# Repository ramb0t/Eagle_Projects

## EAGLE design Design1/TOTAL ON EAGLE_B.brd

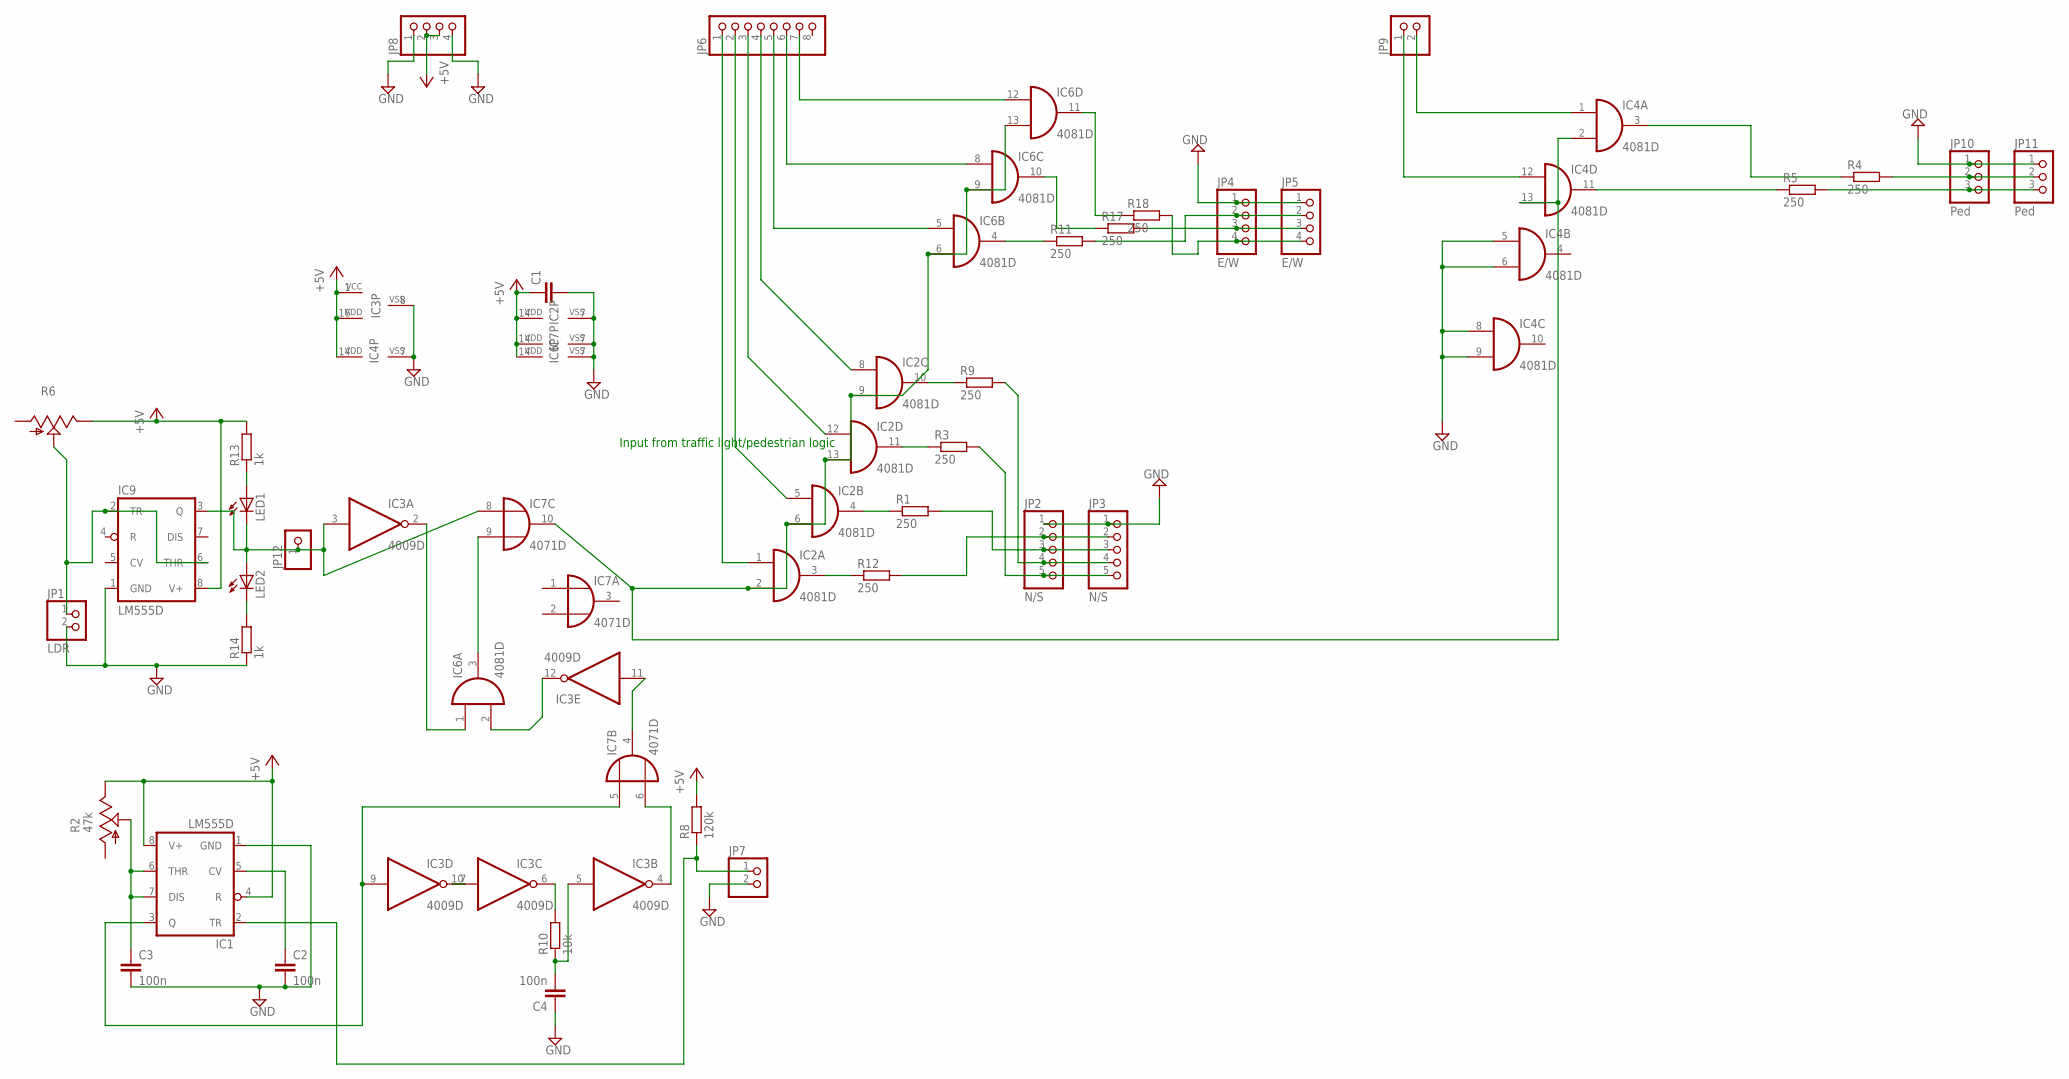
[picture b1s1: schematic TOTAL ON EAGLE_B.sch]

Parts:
C1: C-EUC0805; C0805
C2, C3, C4: 100n; C0805
IC1, IC9: LM555D; SO08
IC2, IC4, IC6: 4081D; SO14
IC3: 4009D; SO16
IC7: 4071D; SO14
JP1: LDR; 1X02
JP2, JP3: N/S; 1X05
JP4, JP5: E/W; 1X04
JP6: PINHD-1X8; 1X08
JP7, JP9: PINHD-1X2; 1X02
JP8: PINHD-1X4; 1X04
JP10, JP11: Ped; 1X03
JP12: PINHD-1X1; 1X01
LED1, LED2: LEDSML0805; SML0805
R1, R3, R4, R5, R9, R11, R12, R17, R18: 250; M0805
R2: 47k; B64W
R6: TRIM_US-B25P; B25P
R8: 120k; M0805
R10: 10k; M0805
R13, R14: 1k; M0805

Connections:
+5V: C1.1, IC1.4 (R), IC1.8 (V+), IC2.14 (VDD), IC3.1 (VCC), IC3.16 (VDD), IC4.14 (VDD), IC6.14 (VDD), IC7.14 (VDD), IC9.8 (V+), JP8.2, JP8.3, R2.E, R6.E, R8.2, R13.2
GND: C1.2, C2.2, C3.2, C4.1, IC1.1 (GND), IC2.7 (VSS), IC3.8 (VSS), IC4.5 (I0), IC4.6 (I1), IC4.7 (VSS), IC4.8 (I0), IC4.9 (I1), IC6.7 (VSS), IC7.7 (VSS), IC9.1 (GND), JP1.2, JP2.1, JP3.1, JP4.1, JP5.1, JP7.2, JP8.1, JP8.4, JP10.1, JP11.1, R14.1
unnamed: C2.1, IC1.5 (CV)
unnamed: IC2.4 (O), R1.1
unnamed: IC3.4 (O), IC7.6 (I1)
unnamed: IC2.3 (O), R12.1
unnamed: JP2.3, JP3.3, R1.2
unnamed: JP10.2, JP11.2, R4.2
unnamed: JP10.3, JP11.3, R5.2
unnamed: JP4.3, JP5.3, R17.2
unnamed: IC4.12 (I0), JP9.1
unnamed: IC4.1 (I0), JP9.2
unnamed: IC2.11 (O), R3.1
unnamed: IC4.3 (O), R4.1
unnamed: JP2.5, JP3.5, R3.2
unnamed: IC1.2 (TR), JP7.1, R8.1
unnamed: IC4.11 (O), R5.1
unnamed: IC2.10 (O), R9.1
unnamed: IC1.3 (Q), IC3.9 (I), IC7.5 (I0)
unnamed: JP2.4, JP3.4, R9.2
unnamed: IC3.2 (O), IC6.1 (I0)
unnamed: IC6.3 (O), IC7.9 (I1)
unnamed: IC3.12 (O), IC6.2 (I1)
unnamed: C3.1, IC1.6 (THR), IC1.7 (DIS), R2.S
unnamed: IC3.7 (I), IC3.10 (O)
unnamed: C4.2, IC3.5 (I), R10.1
unnamed: IC2.2 (I1), IC2.6 (I1), IC2.9 (I1), IC2.13 (I1), IC4.2 (I1), IC4.13 (I1), IC6.6 (I1), IC6.9 (I1), IC6.13 (I1), IC7.10 (O)
unnamed: IC2.1 (I0), JP6.1
unnamed: LED1.A, R13.1
unnamed: IC3.3 (I), IC7.8 (I0), IC9.3 (Q), JP12.1, LED1.C, LED2.A
unnamed: LED2.C, R14.2
unnamed: IC3.6 (O), R10.2
unnamed: IC9.2 (TR), IC9.6 (THR), JP1.1, R6.S
unnamed: IC2.5 (I0), JP6.2
unnamed: IC2.12 (I0), JP6.3
unnamed: IC2.8 (I0), JP6.4
unnamed: IC6.5 (I0), JP6.5
unnamed: JP2.2, JP3.2, R12.2
unnamed: IC6.8 (I0), JP6.6
unnamed: IC6.12 (I0), JP6.7
unnamed: JP4.4, JP5.4, R18.2
unnamed: IC3.11 (I), IC7.4 (O)
unnamed: IC6.11 (O), R18.1
unnamed: IC6.10 (O), R17.1
unnamed: JP4.2, JP5.2, R11.2
unnamed: IC6.4 (O), R11.1

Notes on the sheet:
Input from traffic light/pedestrian logic

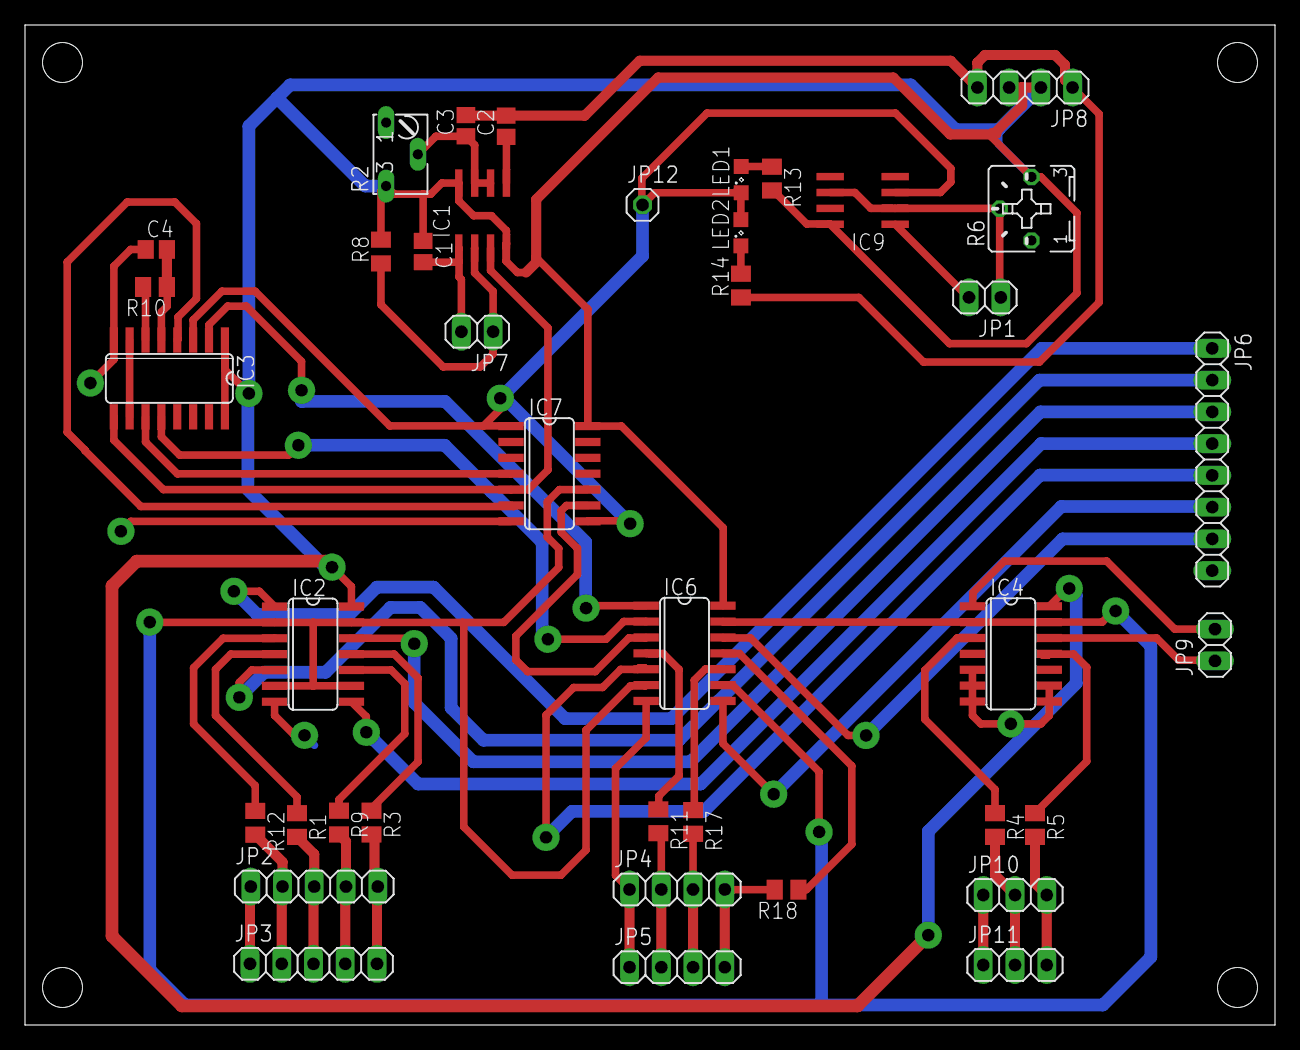
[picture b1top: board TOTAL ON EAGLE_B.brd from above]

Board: 2 copper layers, 100.0 x 80.0 mm, 40 parts (0 on the bottom side), 46 nets.

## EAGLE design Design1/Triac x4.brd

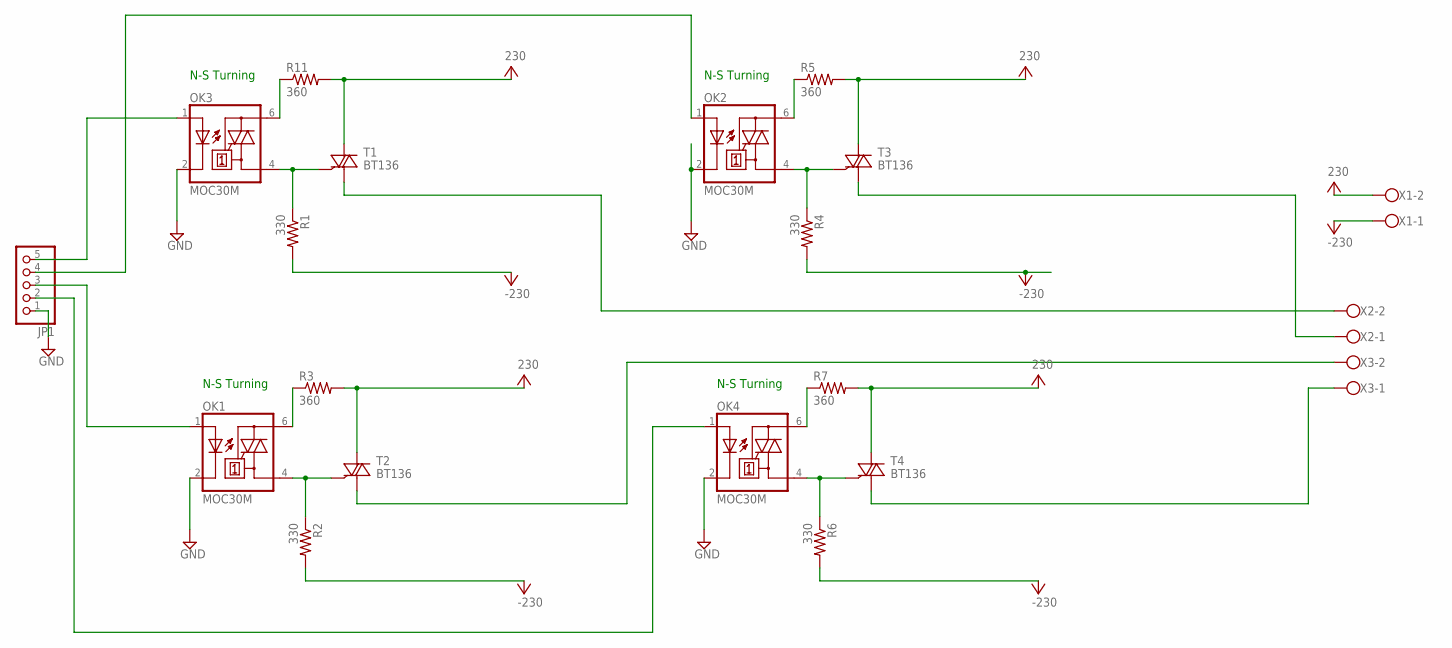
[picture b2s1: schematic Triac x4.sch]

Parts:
JP1: PINHD-1X5; 1X05
OK1, OK2, OK3, OK4: MOC30M; DIL06
R1, R2, R4, R6: 330; 0207/7
R3, R5, R7, R11: 360; 0207/7
T1, T2, T3, T4: BT136; TO220AB
X1, X2, X3: W237-102

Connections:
GND: JP1.1, OK1.2 (C), OK2.2 (C), OK3.2 (C), OK4.2 (C)
unnamed: OK3.6 (A2), R11.1
unnamed: T1.1 (A1), X2.2
unnamed: JP1.5, OK3.1 (A)
unnamed: T2.1 (A1), X3.2
unnamed: OK1.4 (A1), R2.1, T2.3 (G)
unnamed: OK1.6 (A2), R3.1
unnamed: JP1.4, OK2.1 (A)
unnamed: T3.1 (A1), X2.1
unnamed: OK2.4 (A1), R4.1, T3.3 (G)
unnamed: OK2.6 (A2), R5.1
unnamed: JP1.3, OK1.1 (A)
unnamed: T4.1 (A1), X3.1
unnamed: OK4.4 (A1), R6.1, T4.3 (G)
unnamed: OK4.6 (A2), R7.1
unnamed: JP1.2, OK4.1 (A)
unnamed: OK3.4 (A1), R1.1, T1.3 (G)
V+: R3.2, R5.2, R7.2, R11.2, T1.2 (A2), T2.2 (A2), T3.2 (A2), T4.2 (A2), X1.2
V-: R1.2, R2.2, R4.2, R6.2, X1.1

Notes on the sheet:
N-S Turning

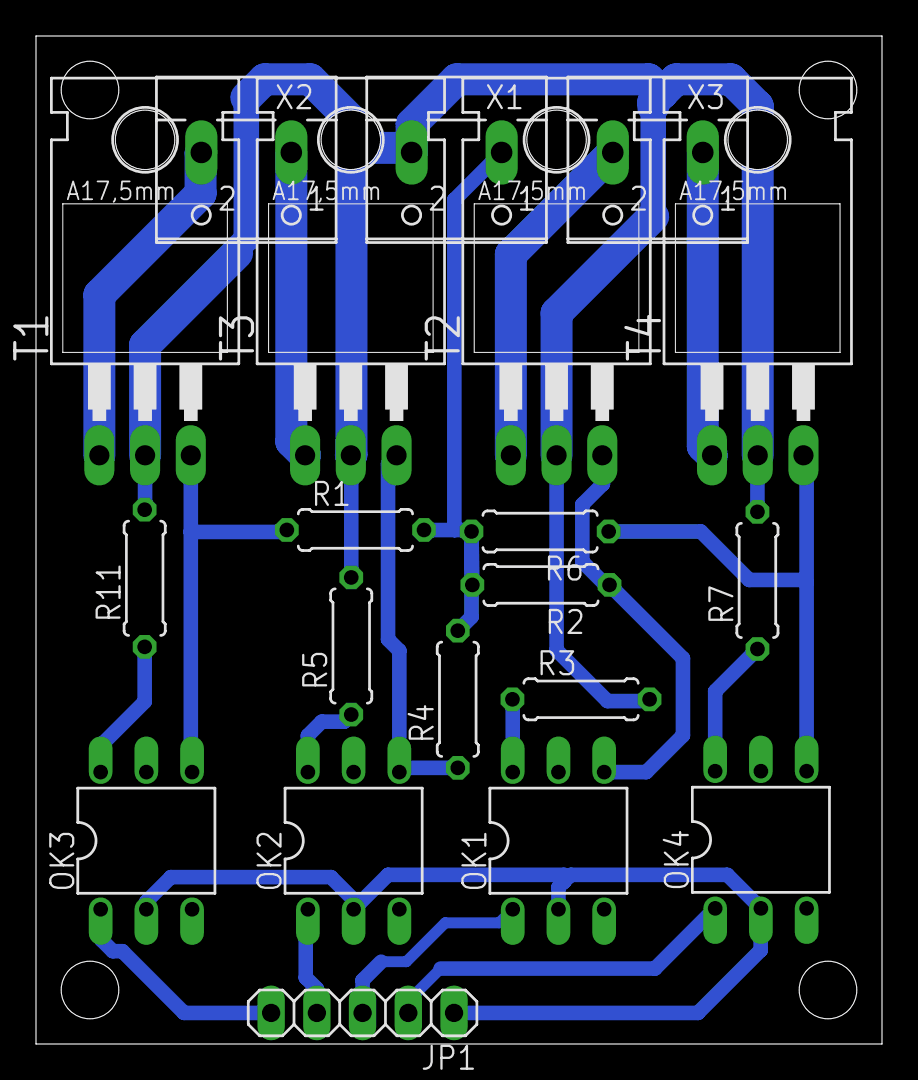
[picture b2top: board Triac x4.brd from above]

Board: 2 copper layers, 47.0 x 56.0 mm, 20 parts (0 on the bottom side), 19 nets.

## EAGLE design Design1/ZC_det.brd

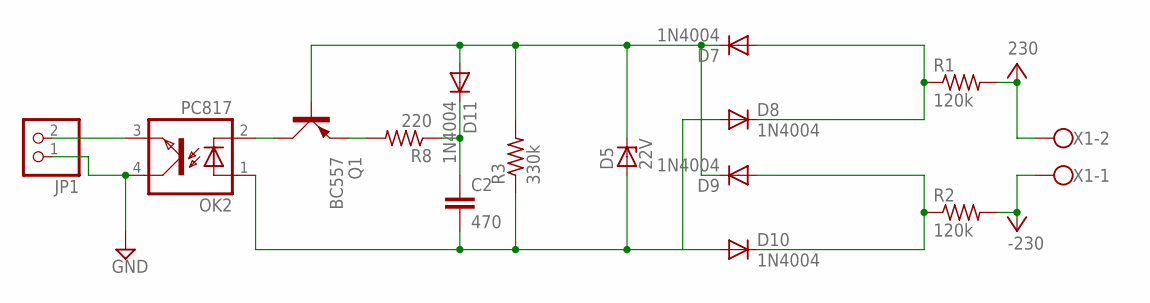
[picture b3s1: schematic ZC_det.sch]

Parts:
C2: 470; C025_050-025X075
D5: 22V; ZDIO-7.5
D7, D8, D9, D10, D11: 1N4004; DO41-10
JP1: PINHD-1X2; 1X02
OK2: PC817; DIL04
Q1: BC557; SOT54A
R1, R2: 120k; 0207/7
R3: 330k; 0207/7
R8: 220; 0207/7
X1: W237-102

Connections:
GND: JP1.1, OK2.4 (COL)
unnamed: JP1.2, OK2.3 (EMIT)
unnamed: Q1.E, R8.2
unnamed: C2.1, D11.C, R8.1
unnamed: OK2.2 (C), Q1.C
unnamed: D7.A, D8.C, R1.1
unnamed: D9.A, D10.C, R2.1
unnamed: D5.C, D7.C, D9.C, D11.A, Q1.B, R3.2
unnamed: C2.2, D5.A, D8.A, D10.A, OK2.1 (A), R3.1
V+: R1.2, X1.2
V-: R2.2, X1.1

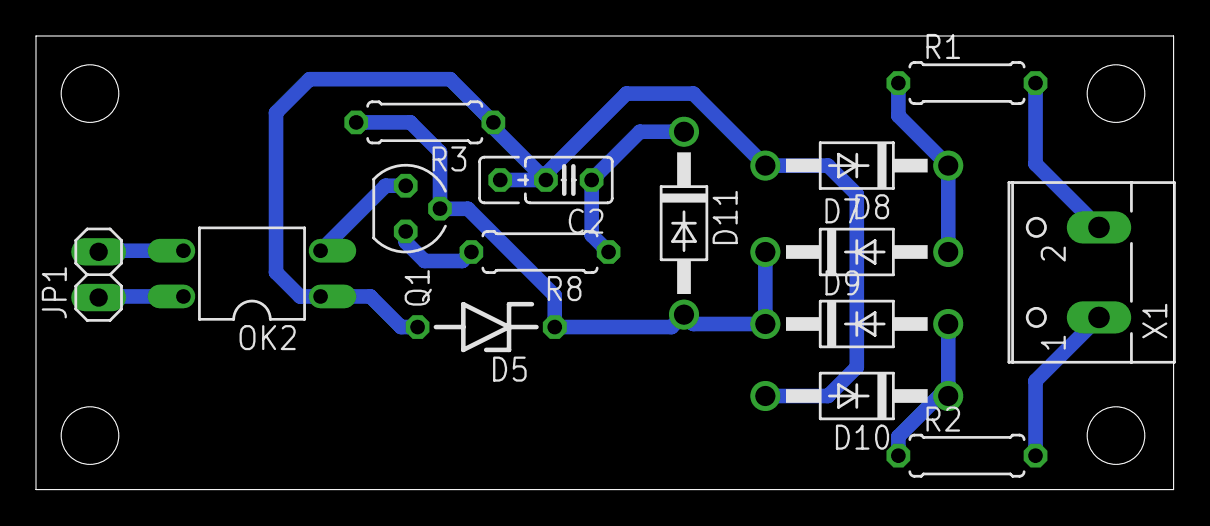
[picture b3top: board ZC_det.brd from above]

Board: 2 copper layers, 63.2 x 25.2 mm, 15 parts (0 on the bottom side), 11 nets.

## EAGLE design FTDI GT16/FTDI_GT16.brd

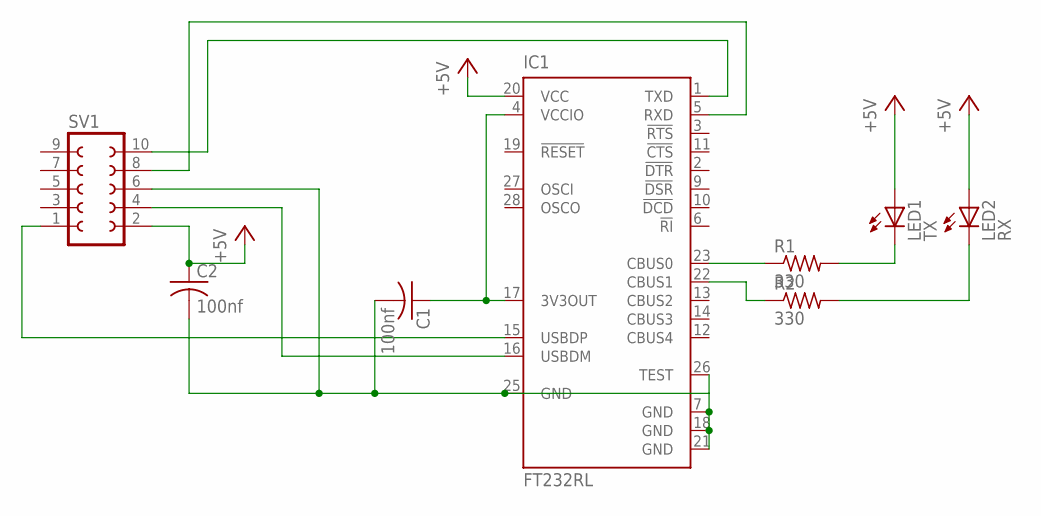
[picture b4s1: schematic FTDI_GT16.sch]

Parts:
C1, C2: 100nf; C0805
IC1: FT232RL; SSOP28
LED1: TX; CHIPLED_0805
LED2: RX; CHIPLED_0805
R1, R2: 330; R0805
SV1: FE05-2

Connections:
+5V: C2.1, IC1.20 (VCC), LED1.A, LED2.A, SV1.2
unnamed: C1.2, C2.2, IC1.7 (GND), IC1.18 (GND), IC1.21 (GND), IC1.25 (GND), IC1.26 (TEST), SV1.6
unnamed: IC1.15 (USBDP), SV1.1
unnamed: IC1.16 (USBDM), SV1.4
unnamed: C1.1, IC1.4 (VCCIO), IC1.17 (3V3OUT)
unnamed: IC1.1 (TXD), SV1.10
unnamed: IC1.5 (RXD), SV1.8
unnamed: IC1.23 (CBUS0), R1.1
unnamed: LED1.C, R1.2
unnamed: LED2.C, R2.2
unnamed: IC1.22 (CBUS1), R2.1

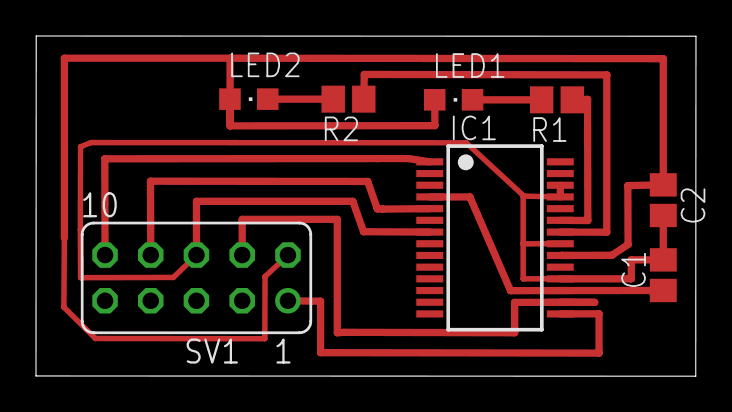
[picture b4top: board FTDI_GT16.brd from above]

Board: 2 copper layers, 36.7 x 18.9 mm, 8 parts (0 on the bottom side), 11 nets.

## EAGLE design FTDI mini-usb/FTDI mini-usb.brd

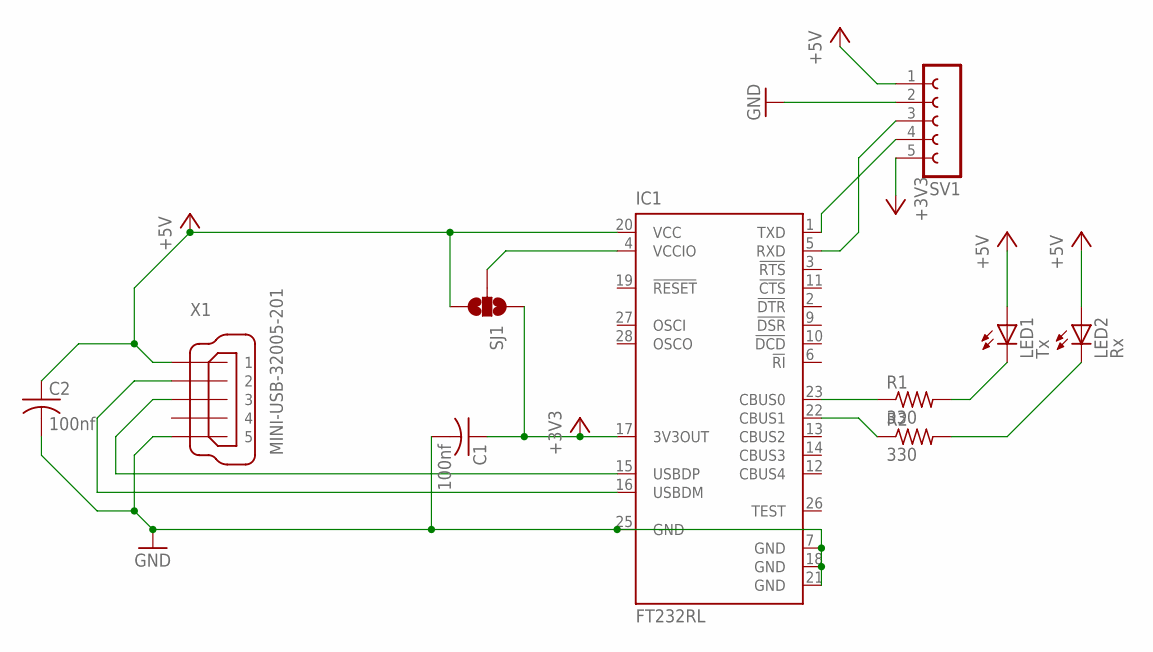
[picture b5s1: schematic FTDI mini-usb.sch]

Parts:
C1, C2: 100nf; C0805K
IC1: FT232RL; SSOP28
LED1: Tx; CHIPLED_0805
LED2: Rx; CHIPLED_0805
R1, R2: 330; R0805W
SJ1: SOLDERJUMPER_2WAYS; SJ_3
SV1: FE05-1
X1: MINI-USB-32005-201; 32005-201

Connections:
+3V3: C1.1, IC1.17 (3V3OUT), SJ1.1, SV1.5
+5V: C2.1, IC1.20 (VCC), LED1.A, LED2.A, SJ1.3, SV1.1, X1.1
GND: C1.2, C2.2, IC1.7 (GND), IC1.18 (GND), IC1.21 (GND), IC1.25 (GND), SV1.2, X1.5
unnamed: IC1.16 (USBDM), X1.2
unnamed: IC1.15 (USBDP), X1.3
unnamed: IC1.4 (VCCIO), SJ1.2
unnamed: IC1.23 (CBUS0), R1.1
unnamed: IC1.22 (CBUS1), R2.1
unnamed: LED1.C, R1.2
unnamed: LED2.C, R2.2
unnamed: IC1.5 (RXD), SV1.3
unnamed: IC1.1 (TXD), SV1.4

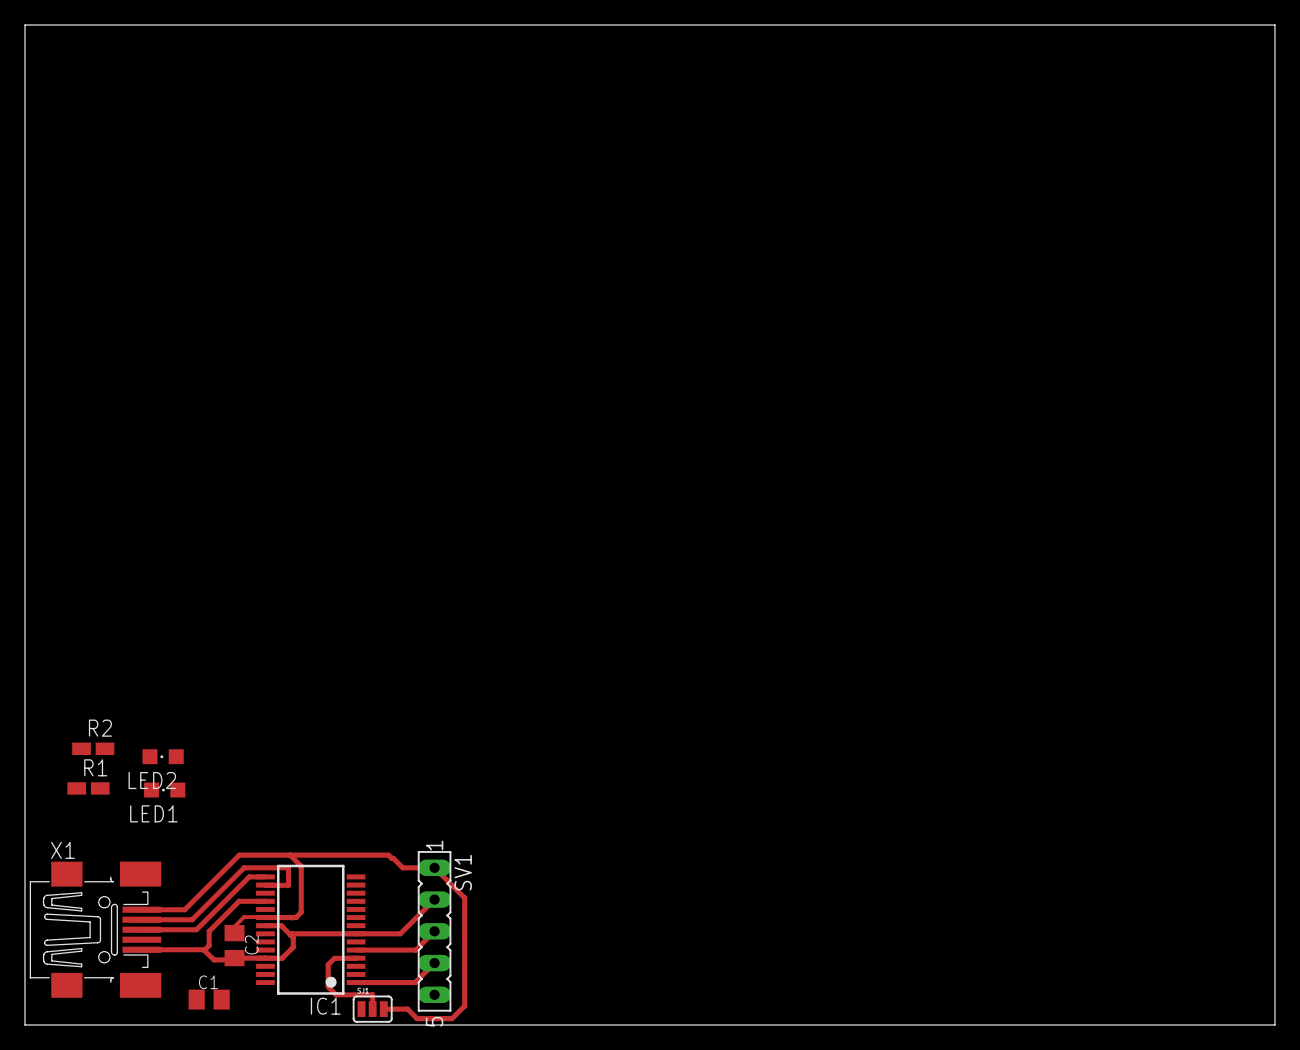
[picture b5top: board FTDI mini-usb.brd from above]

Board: 2 copper layers, 100.0 x 80.0 mm, 10 parts (0 on the bottom side), 12 nets.

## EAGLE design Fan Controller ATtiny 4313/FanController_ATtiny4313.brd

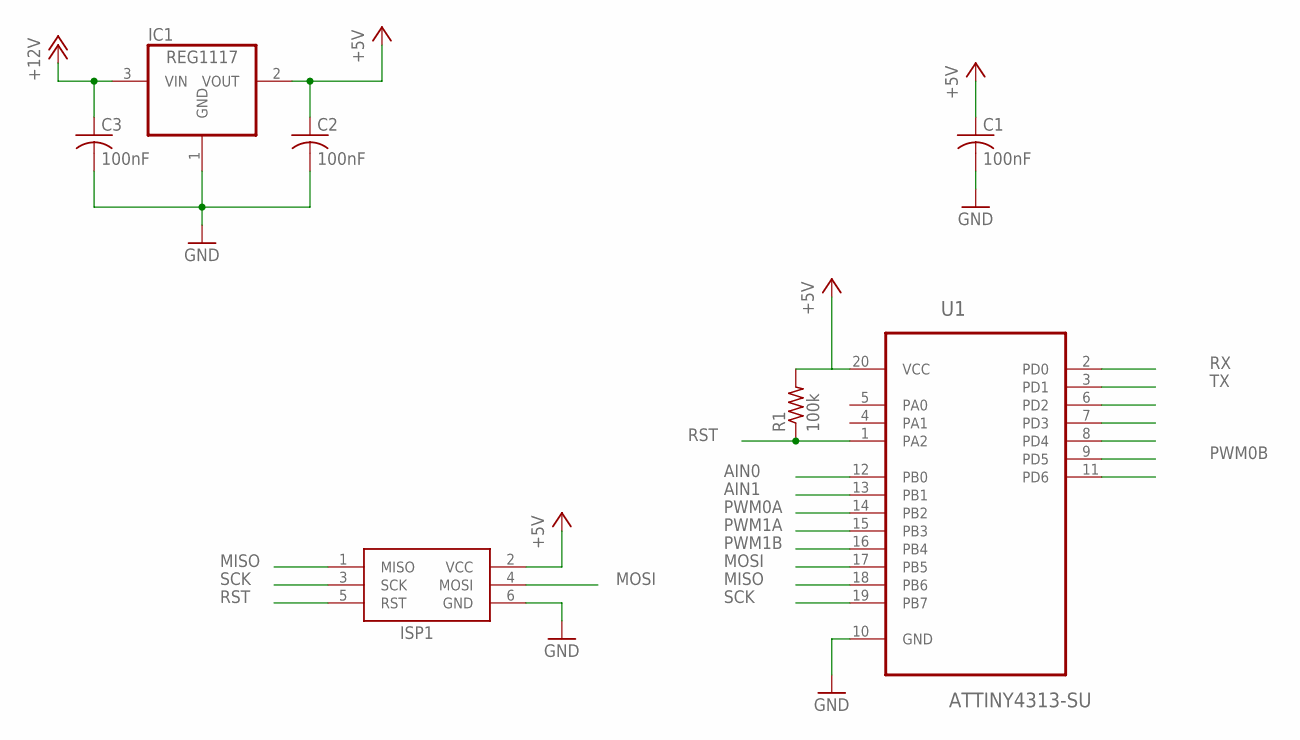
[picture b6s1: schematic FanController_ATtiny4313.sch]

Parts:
C1, C2, C3: 100nF; C0805
IC1: REG1117; SOT223
ISP1: AVRISP-6; AVRISP
R1: 100k; R0805
U1: ATTINY4313-SU; SOIC127P1032X265-20N

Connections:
+5V: C1.1, C2.1, IC1.2 (VOUT), ISP1.2 (VCC), R1.2, U1.20 (VCC)
+12V: C3.1, IC1.3 (VIN)
AIN0: U1.12 (PB0)
AIN1: U1.13 (PB1)
GND: C1.2, C2.2, C3.2, IC1.1 (GND), ISP1.6 (GND), U1.10 (GND)
MISO: ISP1.1 (MISO), U1.18 (PB6)
MOSI: ISP1.4 (MOSI), U1.17 (PB5)
PWM0A: U1.14 (PB2)
PWM0B: U1.9 (PD5)
PWM1A: U1.15 (PB3)
PWM1B: U1.16 (PB4)
RST: ISP1.5 (RST), R1.1, U1.1 (PA2)
RX: U1.2 (PD0)
SCK: ISP1.3 (SCK), U1.19 (PB7)
TX: U1.3 (PD1)

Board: 2 copper layers, 7 parts (0 on the bottom side), 7 nets, no tracks yet.

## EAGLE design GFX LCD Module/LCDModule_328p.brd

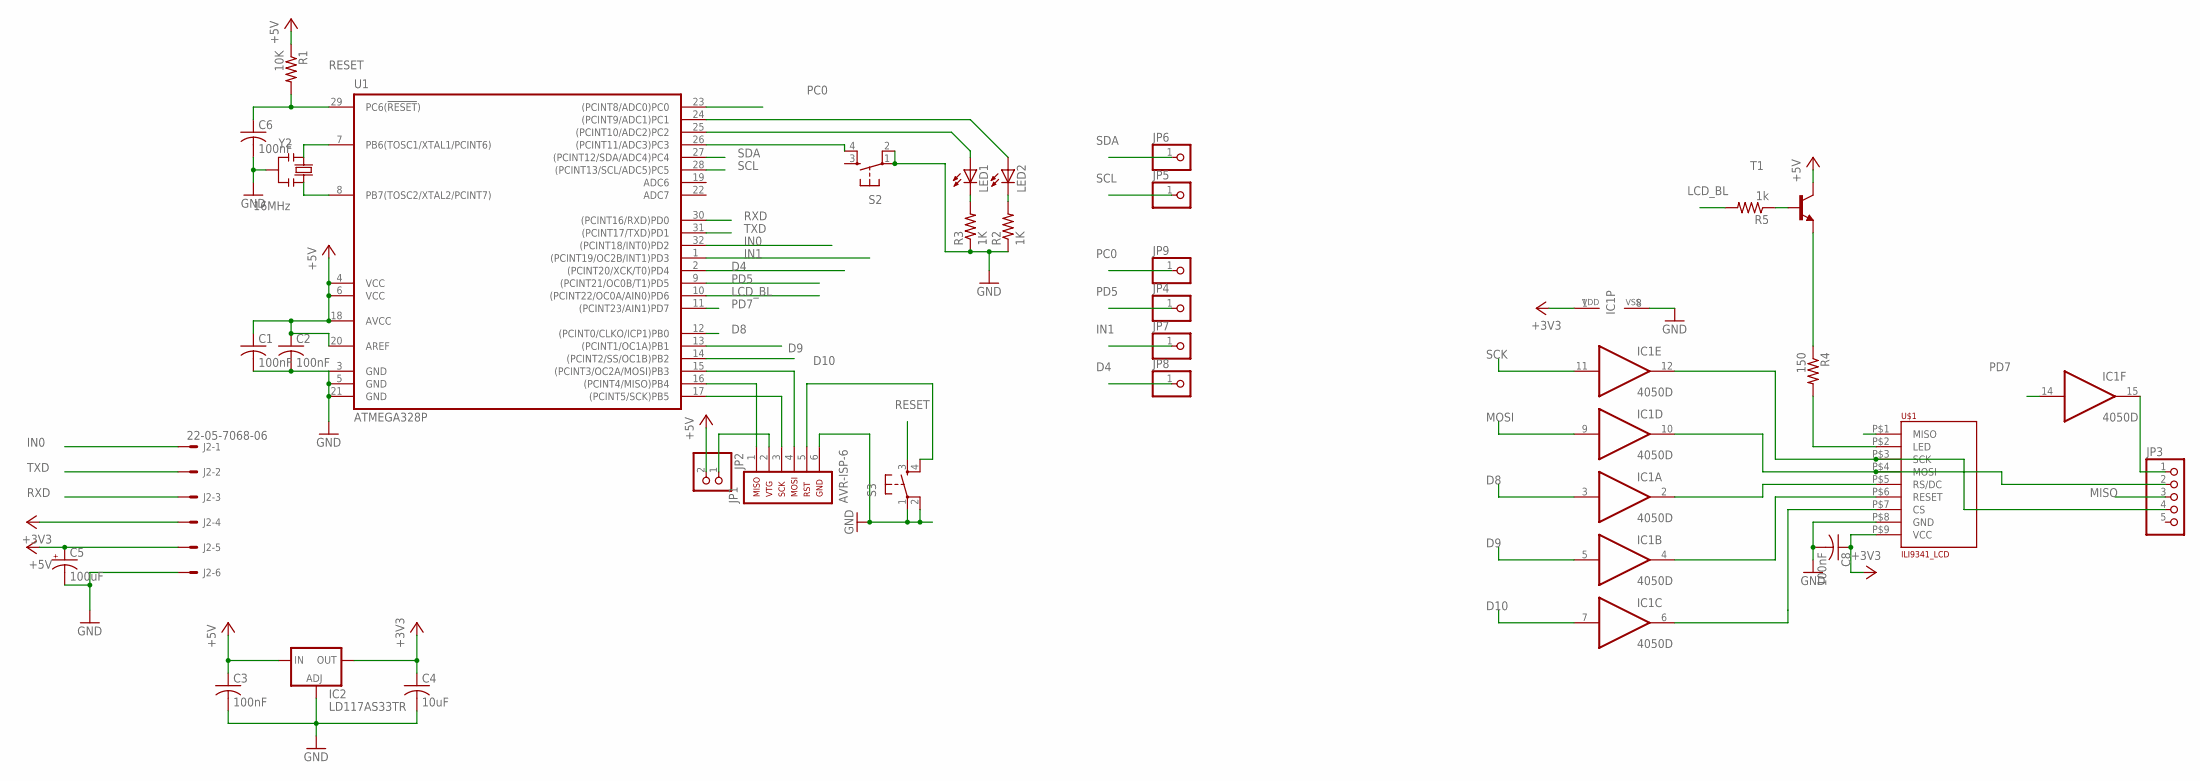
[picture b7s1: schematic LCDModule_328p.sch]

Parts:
C1, C2, C3, C6, C8: 100nF; C0805K
C4: 10uF; C0805K
C5: 100uF; PANASONIC_D
IC1: 4050D; SO16
IC2: LD117AS33TR; SOT223
J2: 22-05-7068-06; 7395-06
JP1: AVR-ISP-6
JP2: PINHD-1X2; 1X02
JP3: PINHD-1X5; 1X05
JP4, JP5, JP6, JP7, JP8, JP9: PINHD-1X1; 1X01
LED1, LED2: LEDCHIPLED_0805; CHIPLED_0805
R1: 10K; R0805
R2, R3: 1K; R0805
R4: 150; R0805
R5: 1k; R0805
S2, S3: TAC_SWITCHSMD; TACTILE_SWITCH_SMD
T1: MMBT2222ALT1-NPN-SOT23-BEC; SOT23-BEC
U1: ATMEGA328P; TQFP32A
U$1: ILI9341_LCD; SIL1X9
Y2: 16MHz; RESONATOR

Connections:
+3V3: C4.1, C8.1, IC1.1 (VDD), IC2.4 (OUT), J2.4, U$1.P$9 (VCC)
+5V: C1.1, C2.1, C3.1, C5.+, IC2.3 (IN), J2.5, JP2.2, R1.1, T1.C, U1.4 (VCC), U1.6 (VCC), U1.18 (AVCC), U1.20 (AREF)
D4: JP8.1, U1.2 ((PCINT20/XCK/T0)PD4)
D8: IC1.3 (I), U1.12 ((PCINT0/CLKO/ICP1)PB0)
D9: IC1.5 (I), U1.13 ((PCINT1/OC1A)PB1)
D10: IC1.7 (I), U1.14 ((PCINT2/SS/OC1B)PB2)
GND: C1.2, C2.2, C3.2, C4.2, C5.-, C6.2, C8.2, IC1.8 (VSS), IC2.1 (ADJ), J2.6, JP1.6, R2.1, R3.1, S2.1, S2.2, S3.1, S3.2, U1.3 (GND), U1.5 (GND), U1.21 (GND), U$1.P$8 (GND), Y2.2
IN0: J2.1, U1.32 ((PCINT18/INT0)PD2)
IN1: JP7.1, U1.1 ((PCINT19/OC2B/INT1)PD3)
LCD_BL: R5.2, U1.10 ((PCINT22/OC0A/AIN0)PD6)
MISO: JP1.1, JP3.3, U1.16 ((PCINT4/MISO)PB4)
MOSI: IC1.9 (I), JP1.4, U1.15 ((PCINT3/OC2A/MOSI)PB3)
unnamed: R5.1, T1.B
unnamed: LED2.A, U1.24 ((PCINT9/ADC1)PC1)
unnamed: LED1.A, U1.25 ((PCINT10/ADC2)PC2)
unnamed: S2.4, U1.26 ((PCINT11/ADC3)PC3)
unnamed: IC1.12 (O), JP3.4, U$1.P$3 (SCK)
unnamed: IC1.10 (O), JP3.2, U$1.P$4 (MOSI)
unnamed: IC1.2 (O), U$1.P$5 (RS/DC)
unnamed: U1.8 (PB7(TOSC2/XTAL2/PCINT7)), Y2.3
unnamed: U1.7 (PB6(TOSC1/XTAL1/PCINT6)), Y2.1
unnamed: LED2.C, R2.2
unnamed: LED1.C, R3.2
unnamed: IC1.4 (O), U$1.P$6 (RESET)
unnamed: IC1.6 (O), U$1.P$7 (CS)
unnamed: IC1.15 (O), JP3.1
unnamed: R4.1, T1.E
unnamed: R4.2, U$1.P$2 (LED)
unnamed: JP1.5, S3.4
unnamed: JP1.2, JP2.1
PC0: JP9.1, U1.23 ((PCINT8/ADC0)PC0)
PD5: JP4.1, U1.9 ((PCINT21/OC0B/T1)PD5)
PD7: IC1.14 (I), U1.11 ((PCINT23/AIN1)PD7)
RESET: C6.1, R1.2, S3.3, U1.29 (PC6(!RESET!))
RXD: J2.3, U1.30 ((PCINT16/RXD)PD0)
SCK: IC1.11 (I), JP1.3, U1.17 ((PCINT5/SCK)PB5)
SCL: JP5.1, U1.28 ((PCINT13/SCL/ADC5)PC5)
SDA: JP6.1, U1.27 ((PCINT12/SDA/ADC4)PC4)
TXD: J2.2, U1.31 ((PCINT17/TXD)PD1)

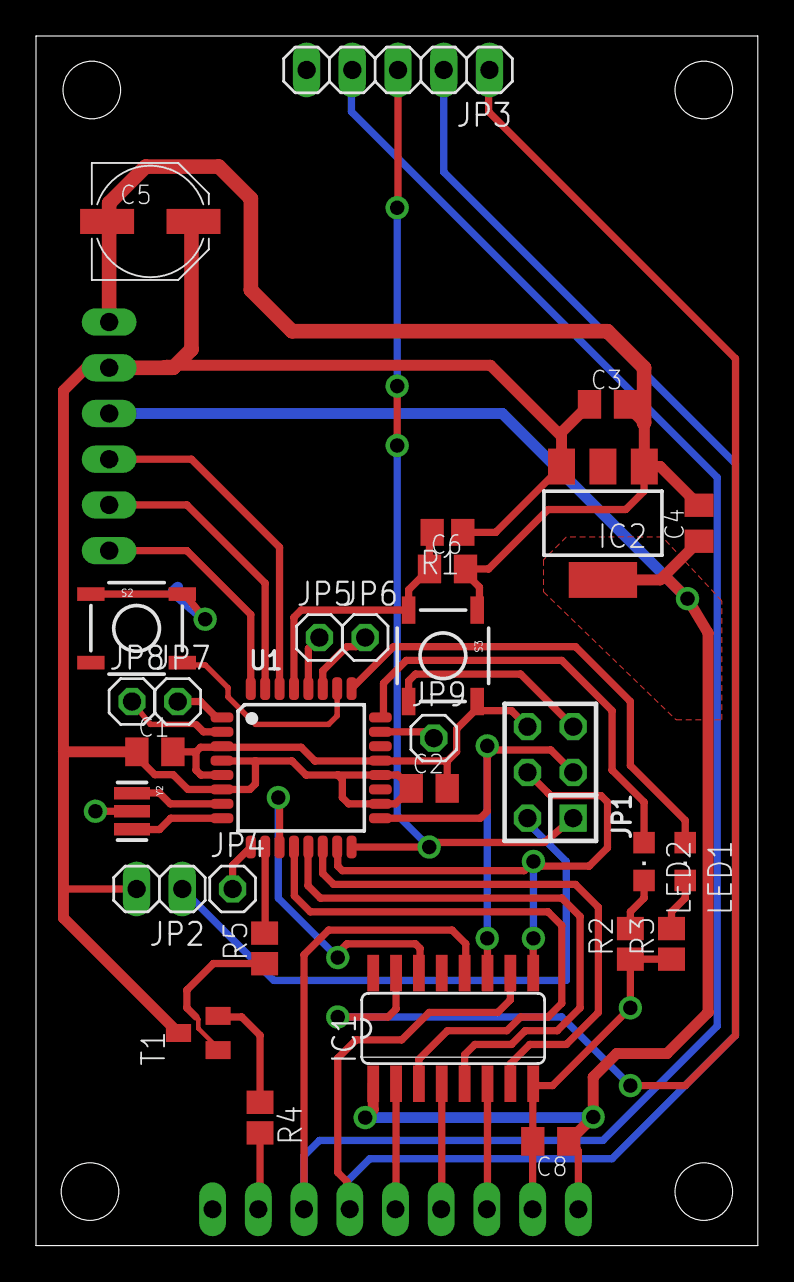
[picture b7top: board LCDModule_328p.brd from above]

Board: 2 copper layers, 40.1 x 67.2 mm, 32 parts (1 on the bottom side), 39 nets.

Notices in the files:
parts and their libraries:
SparkFun: Licensing: CC v3.0 Share-Alike You are welcome to use this library for commercial purposes.
atmel-avr: Copyright (C) 2008, Bob Starr
